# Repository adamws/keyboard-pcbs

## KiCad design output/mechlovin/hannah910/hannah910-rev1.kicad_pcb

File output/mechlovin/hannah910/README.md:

## mechlovin/hannah910/hannah910-rev1

[layout](hannah910-rev1-kle.json) - [PCB](hannah910-rev1.kicad_pcb)

{:loading="lazy"}

[Open in keyboard-layout-editor](http://www.keyboard-layout-editor.com/##@@_x:2.75&c=#777777;&=0,0&_c=#cccccc;&=0,1&=0,2&=0,3&=0,4&=0,5&=0,6&=0,7&=0,8&=0,9&=0,10&=0,11&=0,12&_c=#aaaaaa;&=0,13%0A%0A%0A0,0&=0,14%0A%0A%0A0,0;&@_x:2.75&w:1.5;&=1,0&_c=#cccccc;&=1,1&=1,2&=1,3&=1,4&=1,5&=1,6&=1,7&=1,8&=1,9&=1,10&=1,11&=1,12&_c=#aaaaaa&w:1.5;&=1,13%0A%0A%0A1,0&_c=#cccccc;&=1,14;&@_x:2.75&c=#aaaaaa&w:1.75;&=2,0&_c=#cccccc;&=2,1&=2,2&=2,3&=2,4&=2,5&=2,6&=2,7&=2,8&=2,9&=2,10&=2,11&_c=#777777&w:2.25;&=2,13%0A%0A%0A1,0&_c=#cccccc;&=2,14;&@_x:2.75&c=#aaaaaa&w:1.25;&=3,0%0A%0A%0A3,0&_c=#cccccc;&=3,1%0A%0A%0A3,0&=3,2&=3,3&=3,4&=3,5&=3,6&=3,7&=3,8&=3,9&=3,10&_c=#aaaaaa;&=3,11%0A%0A%0A2,0&_w:1.75;&=3,12%0A%0A%0A2,0&_c=#cccccc;&=3,13&=3,14;&@_x:2.75&c=#aaaaaa&w:1.25;&=4,0%0A%0A%0A4,0&_w:1.25;&=4,1%0A%0A%0A4,0&_w:1.25;&=4,2%0A%0A%0A4,0&_c=#cccccc&w:2.75;&=4,4%0A%0A%0A4,0&_w:1.25;&=4,6%0A%0A%0A4,0&_w:2.25;&=4,8%0A%0A%0A4,0&_c=#aaaaaa&w:1.25;&=4,10%0A%0A%0A4,0&_w:1.25;&=4,11%0A%0A%0A4,0&_x:0.5&c=#cccccc;&=4,12&=4,13&=4,14;&@_x:19.25&y:-5&c=#aaaaaa&w:2;&=0,13%0A%0A%0A0,1;&@_x:20.0&c=#777777&w:1.25&h:2&w2:1.5&h2:1&x2:-0.25;&=2,13%0A%0A%0A1,1;&@_x:19.0&c=#aaaaaa;&=2,12%0A%0A%0A1,1;&@_w:2.25;&=3,0%0A%0A%0A3,1&_x:16.75&w:2.75;&=3,12%0A%0A%0A2,1;&@_x:2.75&y:1.25&w:1.25;&=4,0%0A%0A%0A4,1&_w:1.25;&=4,1%0A%0A%0A4,1&_w:1.25;&=4,2%0A%0A%0A4,1&_c=#cccccc&w:2.25;&=4,4%0A%0A%0A4,1&_w:1.25;&=4,6%0A%0A%0A4,1&_w:2.75;&=4,8%0A%0A%0A4,1&_c=#aaaaaa&w:1.25;&=4,10%0A%0A%0A4,1&_w:1.25;&=4,11%0A%0A%0A4,1;&@_x:2.75&w:1.25;&=4,0%0A%0A%0A4,2&_w:1.25;&=4,1%0A%0A%0A4,2&_w:1.25;&=4,2%0A%0A%0A4,2&_c=#cccccc&w:6.25;&=4,6%0A%0A%0A4,2&_c=#aaaaaa&w:1.25;&=4,10%0A%0A%0A4,2&_w:1.25;&=4,11%0A%0A%0A4,2;&@_x:2.75&w:1.5;&=4,0%0A%0A%0A4,3&=4,1%0A%0A%0A4,3&_w:1.5;&=4,2%0A%0A%0A4,3&_c=#cccccc&w:7;&=4,6%0A%0A%0A4,3&_c=#aaaaaa&w:1.5;&=4,11%0A%0A%0A4,3)

{:loading="lazy"}

## mechlovin/hannah910/hannah910-rev2

[layout](hannah910-rev2-kle.json) - [PCB](hannah910-rev2.kicad_pcb)

{:loading="lazy"}

[Open in keyboard-layout-editor](http://www.keyboard-layout-editor.com/##@@_x:2.75&c=#777777;&=0,0&_c=#cccccc;&=0,1&=0,2&=0,3&=0,4&=0,5&=0,6&=0,7&=0,8&=0,9&=0,10&=0,11&=0,12&_c=#aaaaaa;&=0,13%0A%0A%0A0,0&=0,14%0A%0A%0A0,0&_c=#cccccc;&=4,9;&@_x:2.75&c=#aaaaaa&w:1.5;&=1,0&_c=#cccccc;&=1,1&=1,2&=1,3&=1,4&=1,5&=1,6&=1,7&=1,8&=1,9&=1,10&=1,11&=1,12&_c=#aaaaaa&w:1.5;&=1,13%0A%0A%0A1,0&_c=#cccccc;&=1,14;&@_x:2.75&c=#aaaaaa&w:1.75;&=2,0&_c=#cccccc;&=2,1&=2,2&=2,3&=2,4&=2,5&=2,6&=2,7&=2,8&=2,9&=2,10&=2,11&_c=#777777&w:2.25;&=2,13%0A%0A%0A1,0&_c=#cccccc;&=2,14;&@_x:2.75&c=#aaaaaa&w:1.25;&=3,0%0A%0A%0A3,0&_c=#cccccc;&=3,1%0A%0A%0A3,0&=3,2&=3,3&=3,4&=3,5&=3,6&=3,7&=3,8&=3,9&=3,10&_c=#aaaaaa;&=3,11%0A%0A%0A2,0&_w:1.75;&=3,12%0A%0A%0A2,0&_c=#cccccc;&=3,13&=3,14;&@_x:2.75&c=#aaaaaa&w:1.25;&=4,0%0A%0A%0A4,0&_w:1.25;&=4,1%0A%0A%0A4,0&_w:1.25;&=4,2%0A%0A%0A4,0&_c=#cccccc&w:2.75;&=4,4%0A%0A%0A4,0&_w:1.25;&=4,6%0A%0A%0A4,0&_w:2.25;&=4,8%0A%0A%0A4,0&_c=#aaaaaa&w:1.25;&=4,10%0A%0A%0A4,0&_w:1.25;&=4,11%0A%0A%0A4,0&_x:0.5&c=#cccccc;&=4,12&=4,13&=4,14;&@_x:19.25&y:-5&c=#aaaaaa&w:2;&=0,13%0A%0A%0A0,1;&@_x:20.0&c=#777777&w:1.25&h:2&w2:1.5&h2:1&x2:-0.25;&=2,13%0A%0A%0A1,1;&@_x:19.0&c=#aaaaaa;&=2,12%0A%0A%0A1,1;&@_w:2.25;&=3,0%0A%0A%0A3,1&_x:16.75&w:2.75;&=3,12%0A%0A%0A2,1;&@_x:2.75&y:1.25&w:1.25;&=4,0%0A%0A%0A4,1&_w:1.25;&=4,1%0A%0A%0A4,1&_w:1.25;&=4,2%0A%0A%0A4,1&_c=#cccccc&w:2.25;&=4,4%0A%0A%0A4,1&_w:1.25;&=4,6%0A%0A%0A4,1&_w:2.75;&=4,8%0A%0A%0A4,1&_c=#aaaaaa&w:1.25;&=4,10%0A%0A%0A4,1&_w:1.25;&=4,11%0A%0A%0A4,1;&@_x:2.75&w:1.25;&=4,0%0A%0A%0A4,2&_w:1.25;&=4,1%0A%0A%0A4,2&_w:1.25;&=4,2%0A%0A%0A4,2&_c=#cccccc&w:6.25;&=4,6%0A%0A%0A4,2&_c=#aaaaaa&w:1.25;&=4,10%0A%0A%0A4,2&_w:1.25;&=4,11%0A%0A%0A4,2;&@_x:2.75&w:1.5;&=4,0%0A%0A%0A4,3&=4,1%0A%0A%0A4,3&_w:1.5;&=4,2%0A%0A%0A4,3&_c=#cccccc&w:7;&=4,6%0A%0A%0A4,3&_c=#aaaaaa&w:1.5;&=4,11%0A%0A%0A4,3)

{:loading="lazy"}

## mechlovin/hannah910/hannah910-rev3

[layout](hannah910-rev3-kle.json) - [PCB](hannah910-rev3.kicad_pcb)

{:loading="lazy"}

[Open in keyboard-layout-editor](http://www.keyboard-layout-editor.com/##@@_x:2.75&c=#777777;&=0,0&_c=#cccccc;&=0,1&=0,2&=0,3&=0,4&=0,5&=0,6&=0,7&=0,8&=0,9&=0,10&=0,11&=0,12&_c=#aaaaaa;&=0,13%0A%0A%0A0,0&=0,14%0A%0A%0A0,0&_c=#cccccc;&=4,8;&@_x:2.75&c=#aaaaaa&w:1.5;&=1,0&_c=#cccccc;&=1,1&=1,2&=1,3&=1,4&=1,5&=1,6&=1,7&=1,8&=1,9&=1,10&=1,11&=1,12&_c=#aaaaaa&w:1.5;&=1,13%0A%0A%0A1,0&_c=#cccccc;&=1,14;&@_x:2.75&c=#aaaaaa&w:1.75;&=2,0&_c=#cccccc;&=2,1&=2,2&=2,3&=2,4&=2,5&=2,6&=2,7&=2,8&=2,9&=2,10&=2,11&_c=#777777&w:2.25;&=2,13%0A%0A%0A1,0&_c=#cccccc;&=2,14;&@_x:2.75&c=#aaaaaa&w:1.25;&=3,0%0A%0A%0A3,0&_c=#cccccc;&=3,1%0A%0A%0A3,0&=3,2&=3,3&=3,4&=3,5&=3,6&=3,7&=3,8&=3,9&=3,10&_c=#aaaaaa;&=3,11%0A%0A%0A2,0&_w:1.75;&=3,12%0A%0A%0A2,0&_c=#cccccc;&=3,13&=3,14;&@_x:2.75&c=#aaaaaa&w:1.25;&=4,0%0A%0A%0A4,0&_w:1.25;&=4,1%0A%0A%0A4,0&_w:1.25;&=4,2%0A%0A%0A4,0&_c=#cccccc&w:2.75;&=4,3%0A%0A%0A4,0&_w:1.25;&=4,6%0A%0A%0A4,0&_w:2.25;&=4,7%0A%0A%0A4,0&_c=#aaaaaa&w:1.25;&=4,9%0A%0A%0A4,0&_w:1.25;&=4,10%0A%0A%0A4,0&_x:0.5&c=#cccccc;&=4,12&=4,13&=4,14;&@_x:19.25&y:-5&c=#aaaaaa&w:2;&=0,13%0A%0A%0A0,1;&@_x:20.0&c=#777777&w:1.25&h:2&w2:1.5&h2:1&x2:-0.25;&=2,13%0A%0A%0A1,1;&@_x:19.0&c=#aaaaaa;&=2,12%0A%0A%0A1,1;&@_w:2.25;&=3,0%0A%0A%0A3,1&_x:16.75&w:2.75;&=3,12%0A%0A%0A2,1;&@_x:2.75&y:1.25&w:1.25;&=4,0%0A%0A%0A4,1&_w:1.25;&=4,1%0A%0A%0A4,1&_w:1.25;&=4,2%0A%0A%0A4,1&_c=#cccccc&w:2.25;&=4,3%0A%0A%0A4,1&_w:1.25;&=4,6%0A%0A%0A4,1&_w:2.75;&=4,7%0A%0A%0A4,1&_c=#aaaaaa&w:1.25;&=4,9%0A%0A%0A4,1&_w:1.25;&=4,10%0A%0A%0A4,1;&@_x:2.75&w:1.25;&=4,0%0A%0A%0A4,2&_w:1.25;&=4,1%0A%0A%0A4,2&_w:1.25;&=4,2%0A%0A%0A4,2&_c=#cccccc&w:6.25;&=4,6%0A%0A%0A4,2&_c=#aaaaaa&w:1.25;&=4,9%0A%0A%0A4,2&_w:1.25;&=4,10%0A%0A%0A4,2;&@_x:2.75&w:1.5;&=4,0%0A%0A%0A4,3&=4,1%0A%0A%0A4,3&_w:1.5;&=4,2%0A%0A%0A4,3&_c=#cccccc&w:7;&=4,6%0A%0A%0A4,3&_c=#aaaaaa&w:1.5;&=4,10%0A%0A%0A4,3;&@_x:2.75&w:1.25;&=4,0%0A%0A%0A4,4&_w:1.25;&=4,1%0A%0A%0A4,4&_w:1.25;&=4,2%0A%0A%0A4,4&_c=#cccccc&w:2.75;&=4,3%0A%0A%0A4,4&_w:1.25;&=4,6%0A%0A%0A4,4&_w:2.25;&=4,7%0A%0A%0A4,4&_c=#aaaaaa&w:1.5;&=4,9%0A%0A%0A4,4&_w:1.5;&=4,10%0A%0A%0A4,4;&@_x:2.75&w:1.25;&=4,4%0A%0A%0A4,5&_w:1.25;&=4,4%0A%0A%0A4,5&_w:1.25;&=4,4%0A%0A%0A4,5&_c=#cccccc&w:2.25;&=4,3%0A%0A%0A4,5&_w:1.25;&=4,6%0A%0A%0A4,5&_w:2.75;&=4,7%0A%0A%0A4,5&_c=#aaaaaa&w:1.5;&=4,9%0A%0A%0A4,5&_w:1.5;&=4,10%0A%0A%0A4,5;&@_x:2.75&w:1.25;&=4,0%0A%0A%0A4,6&_w:1.25;&=4,1%0A%0A%0A4,6&_w:1.25;&=4,2%0A%0A%0A4,6&_c=#cccccc&w:6.25;&=4,6%0A%0A%0A4,6&_c=#aaaaaa&w:1.5;&=4,9%0A%0A%0A4,6&_w:1.5;&=4,10%0A%0A%0A4,6;&@_x:2.75&w:1.5;&=4,0%0A%0A%0A4,7&_w:1.5;&=4,1%0A%0A%0A4,7&_c=#cccccc&w:7;&=4,6%0A%0A%0A4,7&_c=#aaaaaa&w:1.5;&=4,9%0A%0A%0A4,7&_w:1.5;&=4,10%0A%0A%0A4,7;&@_x:2.75&w:1.25;&=4,0%0A%0A%0A4,8&_w:1.25;&=4,1%0A%0A%0A4,8&_w:1.25;&=4,2%0A%0A%0A4,8&_c=#cccccc&w:6.25;&=4,6%0A%0A%0A4,8&_c=#aaaaaa;&=4,9%0A%0A%0A4,8&=4,10%0A%0A%0A4,8&=4,11%0A%0A%0A4,8;&@_x:2.75&w:1.25;&=4,0%0A%0A%0A4,9&_w:1.25;&=4,1%0A%0A%0A4,9&_w:1.25;&=4,2%0A%0A%0A4,9&_c=#cccccc&w:2.75;&=4,3%0A%0A%0A4,9&_w:1.25;&=4,6%0A%0A%0A4,9&_w:2.25;&=4,7%0A%0A%0A4,9&_c=#aaaaaa;&=4,9%0A%0A%0A4,9&=4,10%0A%0A%0A4,9&=4,11%0A%0A%0A4,9)

{:loading="lazy"}

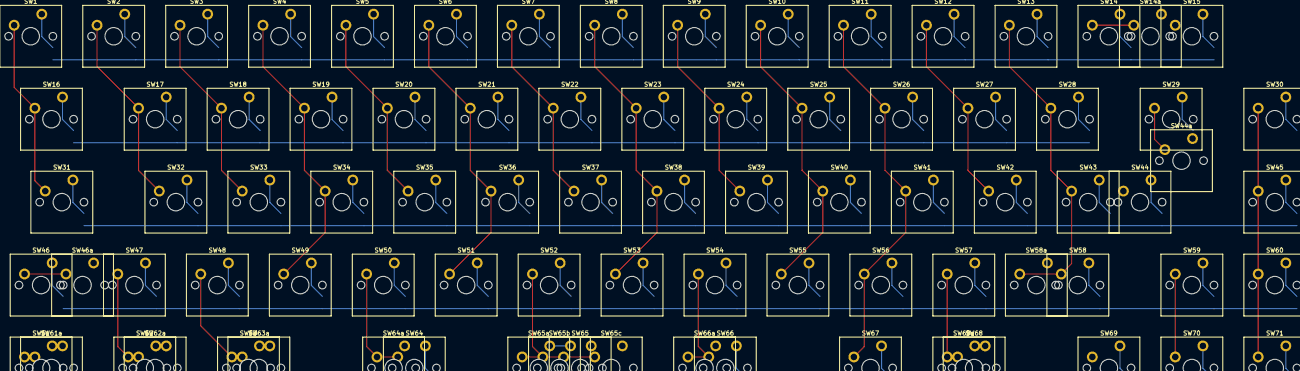
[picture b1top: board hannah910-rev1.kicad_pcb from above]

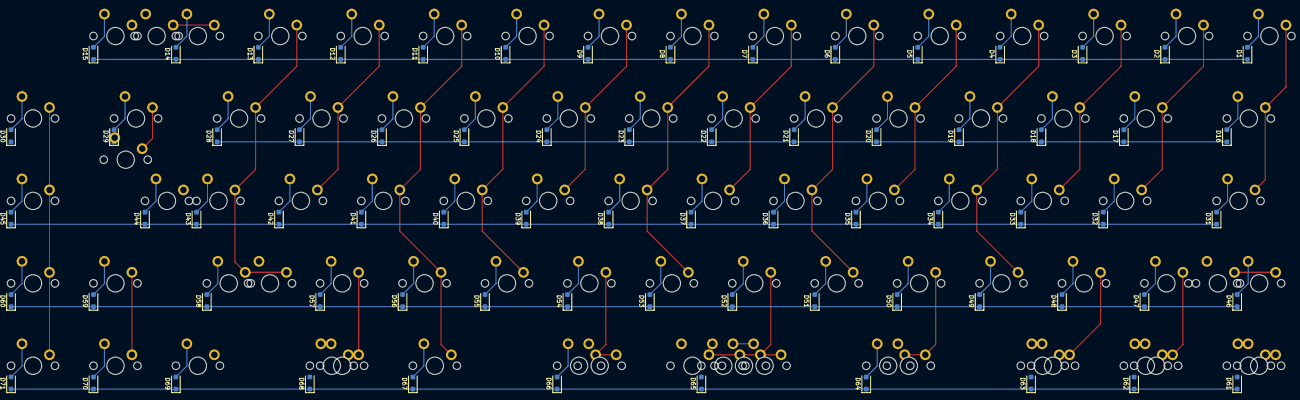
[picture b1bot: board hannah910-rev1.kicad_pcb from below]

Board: 2 copper layers, 155 parts (71 on the bottom side), 91 nets.

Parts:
D1, D2, D3, D4, D5, D6, D7, D8, D9, D10, D11, D12, D13, D14, D15, D16, D17, D18, D19, D20, D21, D22, D23, D24, D25, D26, D27, D28, D29, D30, D31, D32, D33, D34, D35, D36, D37, D38, D39, D40, D41, D42, D43, D44, D45, D46, D47, D48, D49, D50, D51, D52, D53, D54, D55, D56, D57, D58, D59, D60, D61, D62, D63, D64, D65, D66, D67, D68, D69, D70, D71: D_SOD-123F
SW1, SW2, SW3, SW4, SW5, SW6, SW7, SW8, SW9, SW10, SW11, SW12, SW13, SW14, SW14a, SW15, SW16, SW17, SW18, SW19, SW20, SW21, SW22, SW23, SW24, SW25, SW26, SW27, SW28, SW29, SW30, SW31, SW32, SW33, SW34, SW35, SW36, SW37, SW38, SW39, SW40, SW41, SW42, SW43, SW44, SW44a, SW45, SW46, SW46a, SW47, SW48, SW49, SW50, SW51, SW52, SW53, SW54, SW55, SW56, SW57, SW58, SW58a, SW59, SW60, SW61, SW61a, SW62, SW62a, SW63, SW63a, SW64, SW64a, SW65, SW65a, SW65b, SW65c, SW66, SW66a, SW67, SW68, SW68a, SW69, SW70, SW71: SW_Cherry_MX_PCB_1.00u

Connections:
COL0: SW1.1, SW16.1, SW31.1, SW46.1, SW46a.1, SW61.1, SW61a.1
COL1: SW2.1, SW17.1, SW32.1, SW47.1, SW62.1, SW62a.1
COL2: SW3.1, SW18.1, SW33.1, SW48.1, SW63.1, SW63a.1
COL3: SW4.1, SW19.1, SW34.1, SW49.1
COL4: SW5.1, SW20.1, SW35.1, SW50.1, SW64.1, SW64a.1
COL5: SW6.1, SW21.1, SW36.1, SW51.1
COL6: SW7.1, SW22.1, SW37.1, SW52.1, SW65.1, SW65a.1, SW65b.1, SW65c.1
COL7: SW8.1, SW23.1, SW38.1, SW53.1
COL8: SW9.1, SW24.1, SW39.1, SW54.1, SW66.1, SW66a.1
COL9: SW10.1, SW25.1, SW40.1, SW55.1
COL10: SW11.1, SW26.1, SW41.1, SW56.1, SW67.1
COL11: SW12.1, SW27.1, SW42.1, SW57.1, SW68.1, SW68a.1
COL12: SW13.1, SW28.1, SW43.1, SW58.1, SW58a.1, SW69.1
COL13: SW14.1, SW14a.1, SW29.1, SW44.1, SW44a.1, SW59.1, SW70.1
COL14: SW15.1, SW30.1, SW45.1, SW60.1, SW71.1
unnamed: D1.2, SW1.2
unnamed: D2.2, SW2.2
unnamed: D3.2, SW3.2
unnamed: D4.2, SW4.2
unnamed: D5.2, SW5.2
unnamed: D6.2, SW6.2
unnamed: D7.2, SW7.2
unnamed: D8.2, SW8.2
unnamed: D9.2, SW9.2
unnamed: D10.2, SW10.2
unnamed: D11.2, SW11.2
unnamed: D12.2, SW12.2
unnamed: D13.2, SW13.2
unnamed: D14.2, SW14.2, SW14a.2
unnamed: D15.2, SW15.2
unnamed: D16.2, SW16.2
unnamed: D17.2, SW17.2
unnamed: D18.2, SW18.2
unnamed: D19.2, SW19.2
unnamed: D20.2, SW20.2
unnamed: D21.2, SW21.2
unnamed: D22.2, SW22.2
unnamed: D23.2, SW23.2
unnamed: D24.2, SW24.2
unnamed: D25.2, SW25.2
unnamed: D26.2, SW26.2
unnamed: D27.2, SW27.2
unnamed: D28.2, SW28.2
unnamed: D29.2, SW29.2
unnamed: D30.2, SW30.2
unnamed: D31.2, SW31.2
unnamed: D32.2, SW32.2
unnamed: D33.2, SW33.2
unnamed: D34.2, SW34.2
unnamed: D35.2, SW35.2
unnamed: D36.2, SW36.2
unnamed: D37.2, SW37.2
unnamed: D38.2, SW38.2
unnamed: D39.2, SW39.2
unnamed: D40.2, SW40.2
unnamed: D41.2, SW41.2
unnamed: D42.2, SW42.2
unnamed: D43.2, SW43.2
unnamed: D44.2, SW44.2, SW44a.2
unnamed: D45.2, SW45.2
unnamed: D46.2, SW46.2, SW46a.2
unnamed: D47.2, SW47.2
unnamed: D48.2, SW48.2
unnamed: D49.2, SW49.2
unnamed: D50.2, SW50.2
unnamed: D51.2, SW51.2
unnamed: D52.2, SW52.2
unnamed: D53.2, SW53.2
unnamed: D54.2, SW54.2
unnamed: D55.2, SW55.2
unnamed: D56.2, SW56.2
unnamed: D57.2, SW57.2
unnamed: D58.2, SW58.2, SW58a.2
unnamed: D59.2, SW59.2
unnamed: D60.2, SW60.2
unnamed: D61.2, SW61.2, SW61a.2
unnamed: D62.2, SW62.2, SW62a.2
unnamed: D63.2, SW63.2, SW63a.2
unnamed: D64.2, SW64.2, SW64a.2
unnamed: D65.2, SW65.2, SW65a.2, SW65b.2, SW65c.2
unnamed: D66.2, SW66.2, SW66a.2
unnamed: D67.2, SW67.2
unnamed: D68.2, SW68.2, SW68a.2
unnamed: D69.2, SW69.2
unnamed: D70.2, SW70.2
unnamed: D71.2, SW71.2
ROW0: D1.1, D2.1, D3.1, D4.1, D5.1, D6.1, D7.1, D8.1, D9.1, D10.1, D11.1, D12.1, D13.1, D14.1, D15.1
ROW1: D16.1, D17.1, D18.1, D19.1, D20.1, D21.1, D22.1, D23.1, D24.1, D25.1, D26.1, D27.1, D28.1, D29.1, D30.1
ROW2: D31.1, D32.1, D33.1, D34.1, D35.1, D36.1, D37.1, D38.1, D39.1, D40.1, D41.1, D42.1, D43.1, D44.1, D45.1
ROW3: D46.1, D47.1, D48.1, D49.1, D50.1, D51.1, D52.1, D53.1, D54.1, D55.1, D56.1, D57.1, D58.1, D59.1, D60.1
ROW4: D61.1, D62.1, D63.1, D64.1, D65.1, D66.1, D67.1, D68.1, D69.1, D70.1, D71.1
